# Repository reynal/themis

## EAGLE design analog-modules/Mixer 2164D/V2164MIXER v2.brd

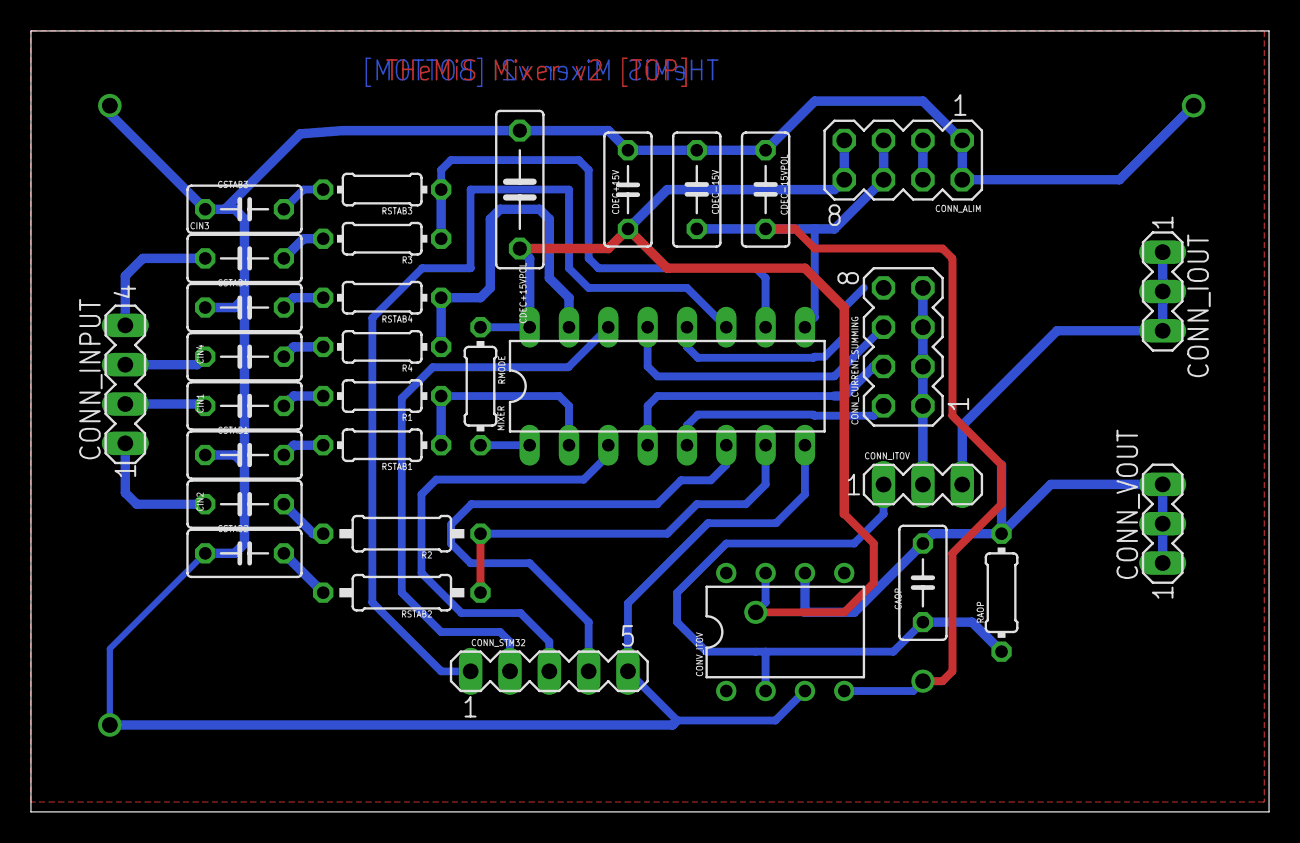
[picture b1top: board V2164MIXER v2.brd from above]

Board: 2 copper layers, 80.0 x 50.4 mm, 32 parts (0 on the bottom side), 32 nets.

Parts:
CAOP: 1p; C050-030X075
CDEC+15V: 100n; C050-030X075
CDEC+15VPOL: 100n; C075-032X103
CDEC-15V, CDEC-15VPOL: 100n; C050-030X075
CIN1, CIN2, CIN3, CIN4: 470n; C050-030X075
CONN_ALIM: MA04-2
CONN_CURRENT_SUMMING: MA04-2
CONN_INPUT: MA04-1
CONN_IOUT: MA03-1
CONN_ITOV: MA03-1
CONN_STM32: MA05-1
CONN_VOUT: MA03-1
CONV_ITOV: NE5534AN; DIL08
CSTAB1, CSTAB2, CSTAB3, CSTAB4: 560p; C050-030X075
MIXER: SSM2164_MULTI; DIL16
R1, R3, R4: 27k; 0204/7
R2: 27k; 0207/10
RAOP: 33K; 0204/7
RMODE: 8.2k; 0204/7
RSTAB1, RSTAB3, RSTAB4: 470; 0204/7
RSTAB2: 470; 0207/10

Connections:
2164_IN1: MIXER.2, R1.1, RSTAB1.1
2164_IN2: MIXER.7, R2.1, RSTAB2.1
2164_IN3: MIXER.10, R3.1, RSTAB3.1
2164_IN4: MIXER.15, R4.1, RSTAB4.1
2164_MODE: MIXER.1, RMODE.2
2164_OUT1: CONN_CURRENT_SUMMING.4, MIXER.4
2164_OUT2: CONN_CURRENT_SUMMING.2, MIXER.5
2164_OUT4: CONN_CURRENT_SUMMING.6, MIXER.13
+5V: CONN_ALIM.3, CONN_ALIM.4
+15V: CDEC+15V.2, CDEC+15VPOL.2, CONN_ALIM.7, CONN_ALIM.8, CONV_ITOV.7, MIXER.16, RMODE.1
-15V: CDEC-15V.1, CDEC-15VPOL.1, CONN_ALIM.5, CONN_ALIM.6, CONV_ITOV.4, MIXER.9
AGND: CDEC+15V.1, CDEC+15VPOL.1, CDEC-15V.2, CDEC-15VPOL.2, CONN_ALIM.1, CONN_ALIM.2, CONN_STM32.5, CONV_ITOV.3, CSTAB1.1, CSTAB2.1, CSTAB3.1, CSTAB4.1, MIXER.8
CURRENT_OUT: CONN_IOUT.1, CONN_IOUT.2, CONN_IOUT.3, CONN_ITOV.3
GAIN1: CONN_STM32.3, MIXER.3
GAIN2: CONN_STM32.4, MIXER.6
GAIN3: CONN_STM32.1, MIXER.11
GAIN4: CONN_STM32.2, MIXER.14
IN1: CIN1.1, CONN_INPUT.2
IN2: CIN2.1, CONN_INPUT.1
IN3: CIN3.1, CONN_INPUT.4
IN4: CIN4.1, CONN_INPUT.3
MIXER_OUT: CONN_CURRENT_SUMMING.1, CONN_CURRENT_SUMMING.3, CONN_CURRENT_SUMMING.5, CONN_CURRENT_SUMMING.7, CONN_ITOV.2
unnamed: CIN4.2, R4.2
unnamed: CSTAB4.2, RSTAB4.2
unnamed: CIN2.2, R2.2
unnamed: CAOP.1, CONN_ITOV.1, CONV_ITOV.2, RAOP.1
unnamed: CSTAB2.2, RSTAB2.2
unnamed: CSTAB1.2, RSTAB1.2
unnamed: CIN1.2, R1.2
unnamed: CSTAB3.2, RSTAB3.2
unnamed: CIN3.2, R3.2
VOLTAGE_OUT: CAOP.2, CONN_VOUT.1, CONN_VOUT.2, CONN_VOUT.3, CONV_ITOV.6, RAOP.2

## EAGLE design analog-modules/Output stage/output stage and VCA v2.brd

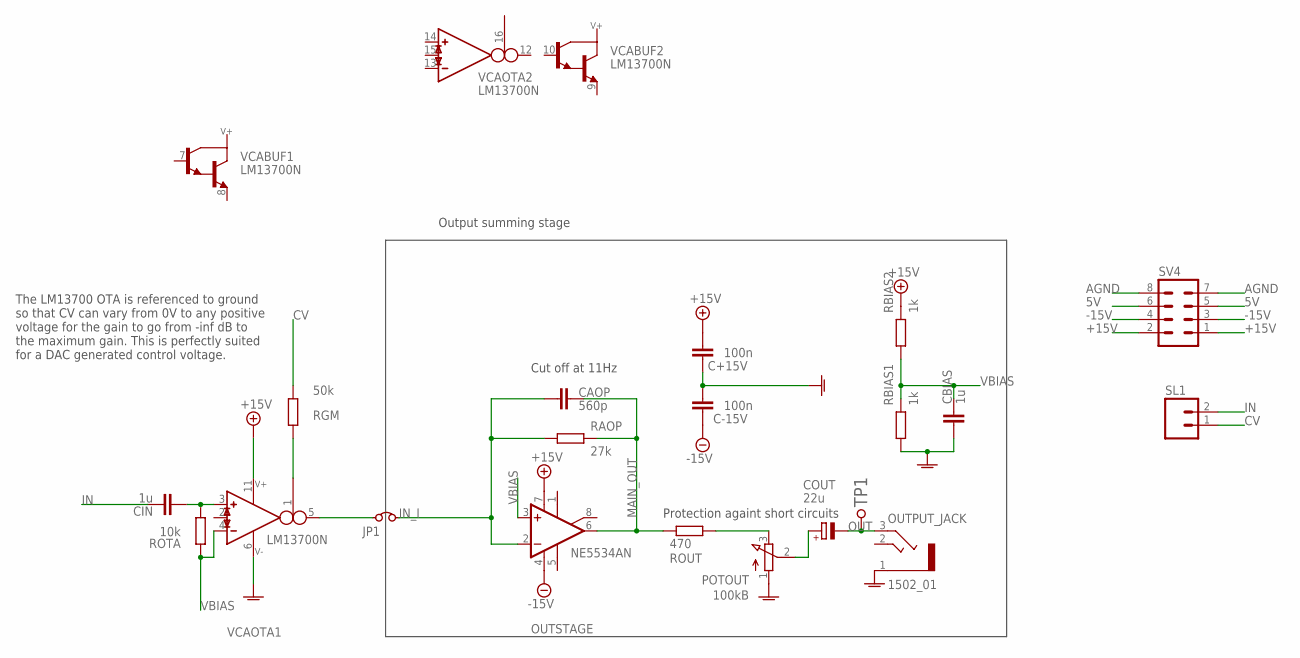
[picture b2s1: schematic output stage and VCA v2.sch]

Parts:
C+15V: 100n; C050-030X075
C-15V: 100n; C050-030X075
CAOP: 560p; C050-030X075
CBIAS: 1u; C050-030X075
CIN: 1u; C050-030X075
COUT: 22u; B45181B
JP1: JUMPER; HDR2X1
OUTPUT_JACK: 1502_01
OUTSTAGE: NE5534AN; DIL08
POTOUT: 100kB; 3RP/1610N
RAOP: 27k; 0204/7
RBIAS1, RBIAS2: 1k; 0204/7
RGM: 50k; 0204/7
ROTA: 10k; 0204/7
ROUT: 470; 0204/7
SL1: MA02; 02PA
SV4: MA04-2
TP1: TESTPOINT; TESTPOINT_63
VCA: LM13700N; DIL16

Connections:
5V: SV4.5, SV4.6
+15V: C+15V.2, OUTSTAGE.7 (V+), RBIAS2.1, SV4.1, SV4.2, VCA.11 (V+)
-15V: C-15V.1, OUTSTAGE.4 (V-), SV4.3, SV4.4
AGND: C+15V.1, C-15V.2, CBIAS.2, OUTPUT_JACK.1, POTOUT.1 (A), RBIAS1.2, SV4.7, SV4.8, VCA.6 (V-)
CV: RGM.1, SL1.1
IN: CIN.1, SL1.2
IN_I: CAOP.2, JP1.2, OUTSTAGE.2 (-IN), RAOP.2
MAIN_OUT: CAOP.1, OUTSTAGE.6 (OUT), RAOP.1, ROUT.2
unnamed: JP1.1, VCA.5 (OUT)
unnamed: RGM.2, VCA.1 (I_BIAS)
unnamed: CIN.2, ROTA.1, VCA.3 (IN_P)
unnamed: COUT.+, POTOUT.2 (S)
unnamed: POTOUT.3 (E), ROUT.1
OUT: COUT.-, OUTPUT_JACK.3 (2), TP1.P$1
VBIAS: CBIAS.1, OUTSTAGE.3 (+IN), RBIAS1.1, RBIAS2.2, ROTA.2, VCA.4 (IN_N)

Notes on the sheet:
Output summing stage
Cut off at 11Hz
Protection againt short circuits
The LM13700 OTA is referenced to ground so that CV can vary from 0V to any positive voltage for the gain to go from -inf dB to the maximum gain. This is perfectly suited for a DAC generated control voltage.

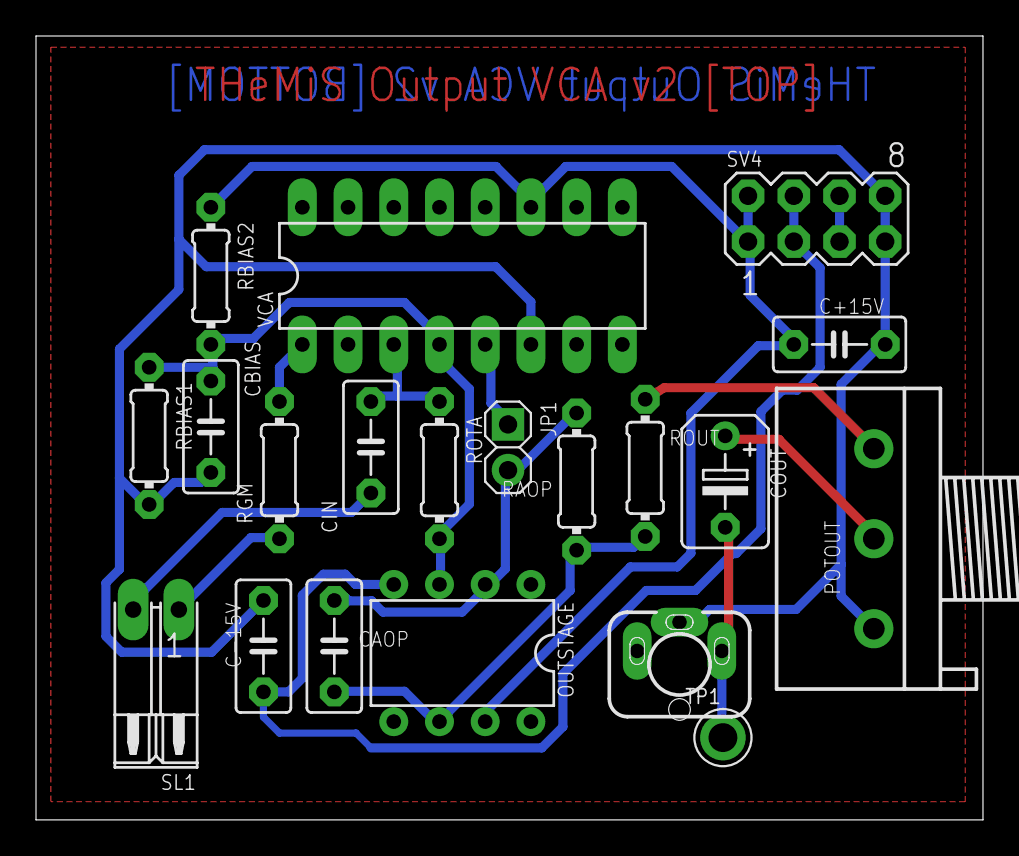
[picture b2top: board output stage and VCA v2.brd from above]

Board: 2 copper layers, 52.6 x 43.5 mm, 20 parts (0 on the bottom side), 15 nets.

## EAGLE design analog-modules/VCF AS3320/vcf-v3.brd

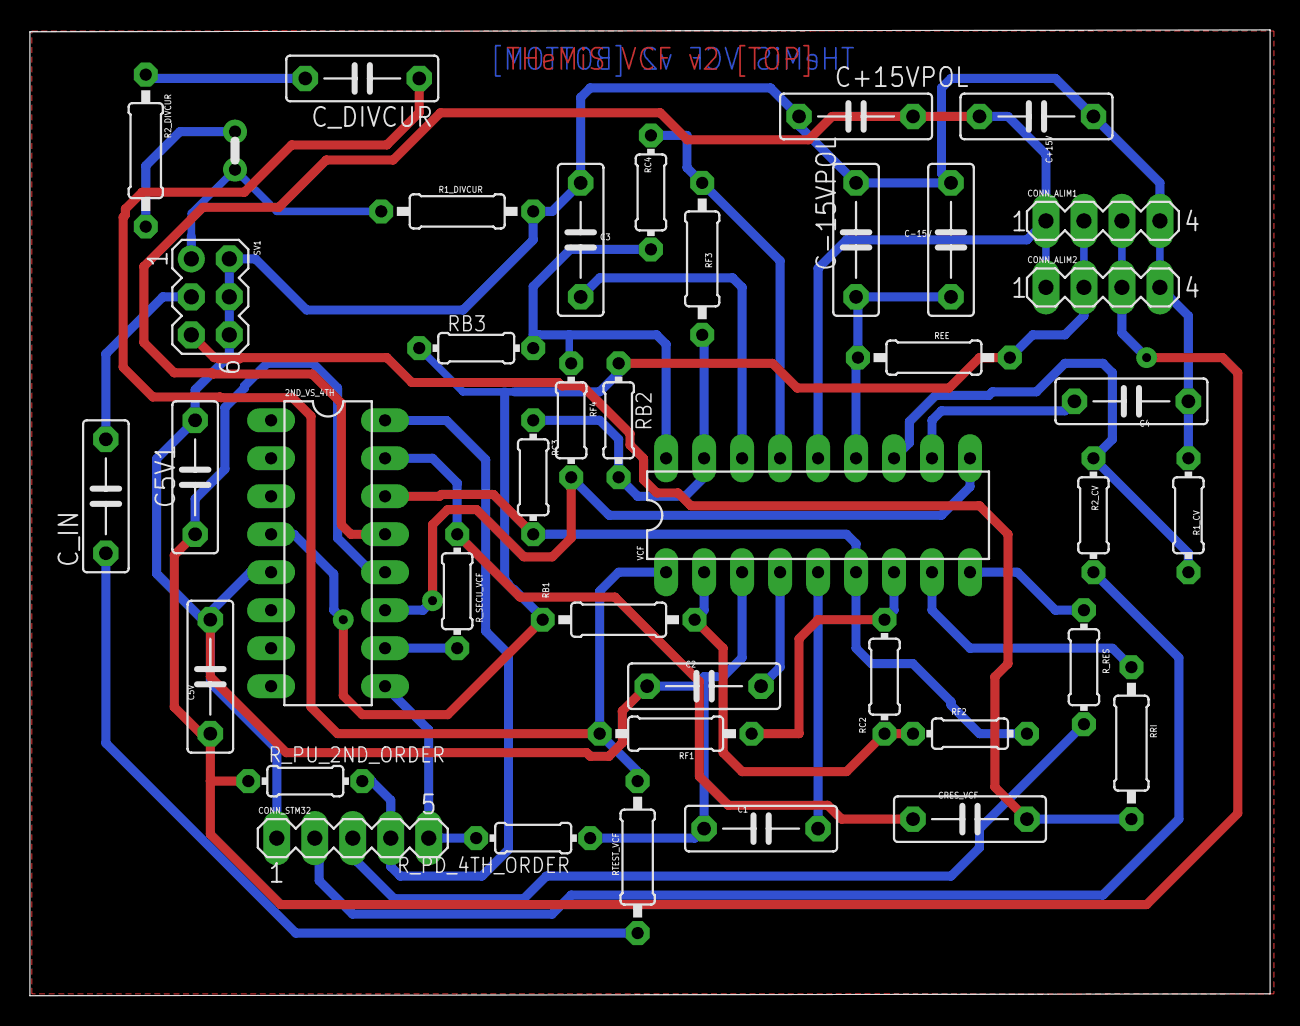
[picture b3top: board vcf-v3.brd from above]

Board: 2 copper layers, 82.9 x 64.6 mm, 41 parts (0 on the bottom side), 32 nets.

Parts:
2ND_VS_4TH: ADG411N; DIL16
C1, C2, C3, C4: 300p; C075-032X103
C5V, C5V1: 100n; C075-032X103
C+15V: 100n; C075-032X103
C+15VPOL: 1u; C075-032X103
C-15V: 100n; C075-032X103
C-15VPOL: 1u; C075-032X103
CONN_ALIM1, CONN_ALIM2: MA04-1
CONN_STM32: MA05-1
CRES_VCF: 1u; C075-032X103
C_DIVCUR: 1u; C075-032X103
C_IN: 470n; C075-032X103
JP_MIXER_OUT: JUMPER_WIRE; JUMPER
R1_CV: 10k; 0204/7
R1_DIVCUR, R2_DIVCUR: 470; 0207/10
R2_CV: 100k; 0204/7
RB1: 220k; 0207/10
RB2, RB3: 220k; 0204/7
RC2, RC3, RC4: 91k; 0204/7
REE: 1.5k; 0207/10
RF1, RF3: 100k; 0207/10
RF2, RF4: 100k; 0204/7
RRI: 51k; 0207/10
RTEST_VCF: 91k; 0207/10
R_PD_4TH_ORDER: 100k; 0204/7
R_PU_2ND_ORDER: 100k; 0204/7
R_RES: 100k; 0204/7
R_SECU_VCF: 1k; 0204/7
SV1: MA03-2
VCF: AS3320; DIL18

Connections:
5V: 2ND_VS_4TH.12, C5V.1, C5V1.1, CONN_ALIM1.3, CONN_ALIM2.3, R_PU_2ND_ORDER.1
+15V: 2ND_VS_4TH.13, C+15V.2, C+15VPOL.2, CONN_ALIM1.1, CONN_ALIM2.1, VCF.14
-15V: 2ND_VS_4TH.4, CONN_ALIM1.2, CONN_ALIM2.2, RB1.1, RB2.1, RB3.1, REE.1
AGND: 2ND_VS_4TH.5, C1.1, C2.1, C3.1, C4.1, C5V.2, C5V1.2, C+15V.1, C+15VPOL.1, C-15V.2, C-15VPOL.2, CONN_ALIM1.4, CONN_ALIM2.4, CONN_STM32.1, R1_CV.2, R1_DIVCUR.2, R_PD_4TH_ORDER.1, SV1.2, SV1.4, SV1.6, VCF.3
CV_CUTOFF: CONN_STM32.2, R2_CV.2
CV_RES: CONN_STM32.3, R_RES.2
IN2: RB1.2, RC2.1, RF2.1, VCF.2
IN3: RB2.2, RC3.1, RF3.1, VCF.17
IN4: RB3.2, RC4.1, RF4.1, VCF.18
IN_2NDORDER: 2ND_VS_4TH.16, CONN_STM32.4, R_PU_2ND_ORDER.2
IN_4THORDER: 2ND_VS_4TH.9, CONN_STM32.5, R_PD_4TH_ORDER.2
I_IN: JP_MIXER_OUT.1, R1_DIVCUR.1, SV1.1
unnamed: C_IN.1, RTEST_VCF.1
unnamed: 2ND_VS_4TH.15, CRES_VCF.1, R_SECU_VCF.1
unnamed: 2ND_VS_4TH.10, R_SECU_VCF.2
unnamed: C_DIVCUR.2, R2_DIVCUR.1
unnamed: JP_MIXER_OUT.2, R2_DIVCUR.2
OUT: CRES_VCF.2, RRI.2, SV1.5
OUT1: RC2.2, RF1.1, VCF.7
OUT2: 2ND_VS_4TH.14, RC3.2, RF2.2, VCF.6
OUT3: RC4.2, RF3.2, VCF.15
OUT4: 2ND_VS_4TH.11, RF4.2, VCF.10
VCAP1: C1.2, VCF.5
VCAP2: C2.2, VCF.4
VCAP3: C3.2, VCF.16
VCAP4: C4.2, VCF.11
VCF_FREQ_CV: R1_CV.1, R2_CV.1, VCF.12
VCF_IN: C_DIVCUR.1, RF1.2, RTEST_VCF.2, VCF.1
VCF_RES_CUR: R_RES.1, VCF.9
VEE: C-15V.1, C-15VPOL.1, REE.2, VCF.13
VIN_RES: RRI.1, VCF.8
V_IN: C_IN.2, SV1.3

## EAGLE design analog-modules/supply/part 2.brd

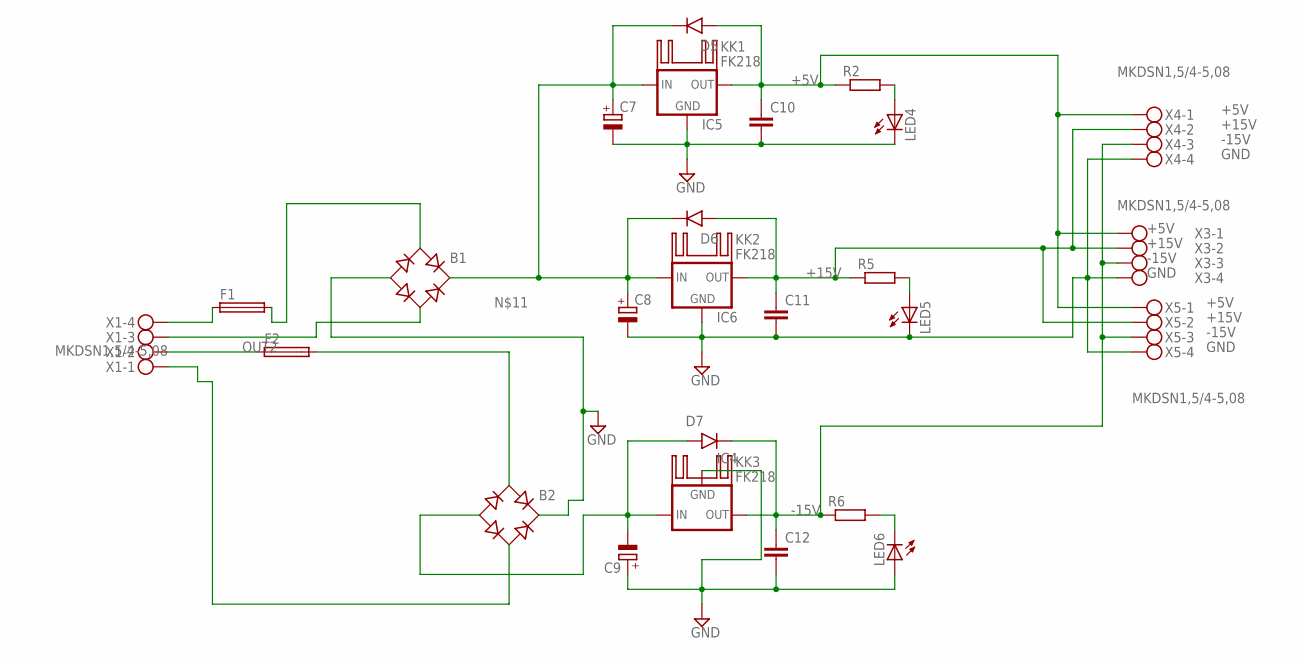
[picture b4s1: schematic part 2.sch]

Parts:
B1, B2: RB1A
C7, C8, C9: CPOL-EUE7.5-18; E7,5-18
C10, C11, C12: C-EU050-025X075; C050-025X075
D5, D6, D7: 1N4001; DO41-10
F1, F2: SH22,5A
IC4: 79XXS
IC5, IC6: 78XXS
KK1, KK2, KK3: FK218
LED4, LED5, LED6: LED5MM
R2, R5, R6: R-EU_0207/15; 0207/15
X1, X3, X4, X5: MKDSN1,5/4-5,08

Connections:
+5V: C10.1, D5.A (ANODE), IC5.OUT, R2.1, X3.1, X4.1, X5.1
+15V: C11.1, D6.A (ANODE), IC6.OUT, R5.1, X3.2, X4.2, X5.2
-15V: C12.1, D7.C (CATHODE), IC4.OUT, R6.1, X3.3, X4.3, X5.3
GND: B1.-, B2.+, C7.-, C8.-, C9.+, C10.2, C11.2, C12.2, IC4.GND, IC5.GND, IC6.GND, LED4.K (C), LED5.K (C), LED6.A, X3.4, X4.4, X5.4
unnamed: B1.AC1, F1.2
unnamed: F1.1, X1.4
unnamed: F2.1, X1.2
unnamed: B2.AC2, X1.1
unnamed: LED5.A, R5.2
unnamed: B2.-, C9.-, D7.A (ANODE), IC4.IN
unnamed: B1.+, C7.+, C8.+, D5.C (CATHODE), D6.C (CATHODE), IC5.IN, IC6.IN
unnamed: B2.AC1, F2.2
unnamed: LED4.A, R2.2
unnamed: LED6.K (C), R6.2
OUT2: B1.AC2, X1.3

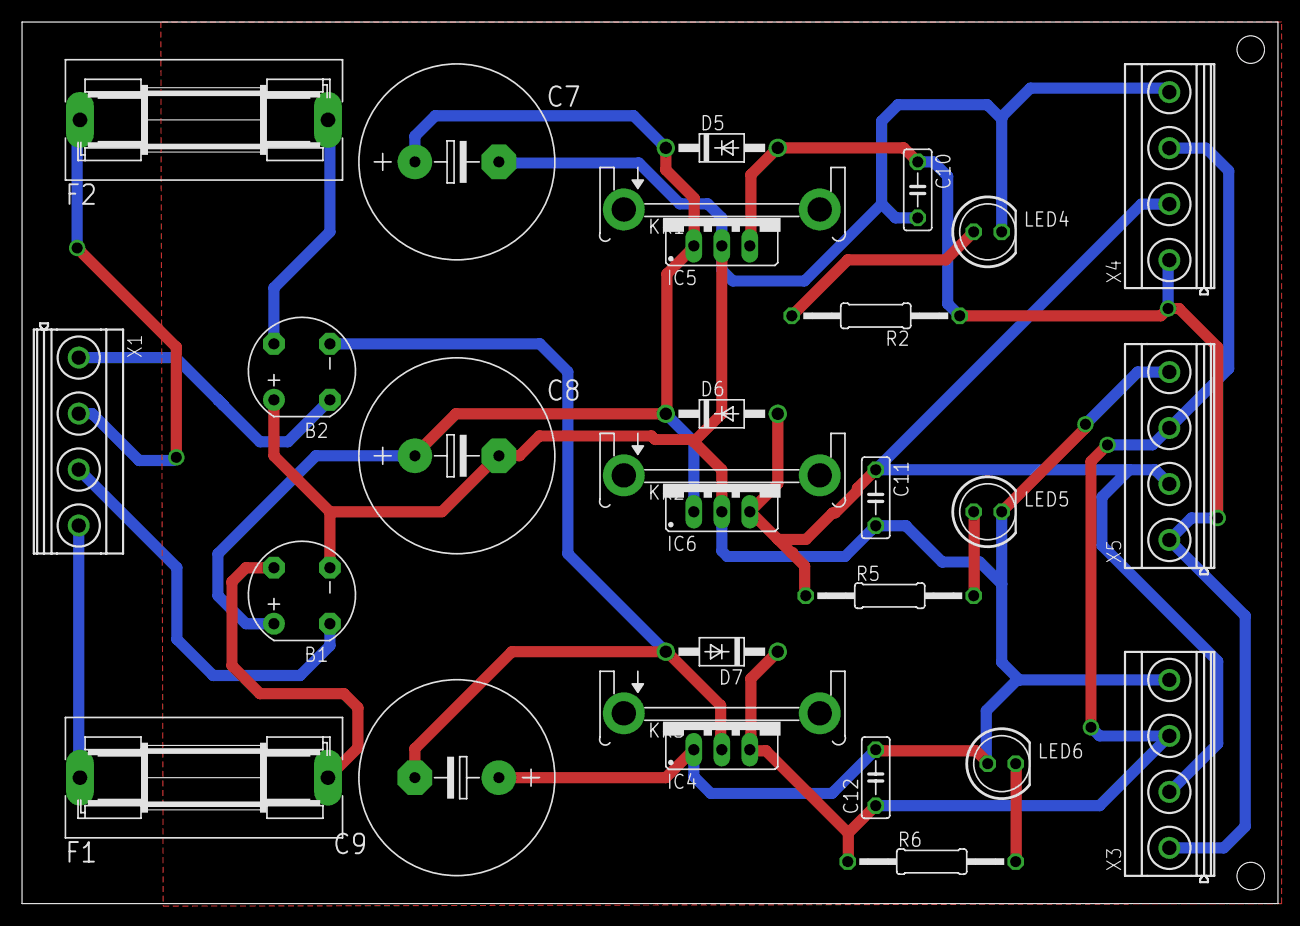
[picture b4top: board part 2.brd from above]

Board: 2 copper layers, 114.0 x 80.0 mm, 29 parts (0 on the bottom side), 15 nets.

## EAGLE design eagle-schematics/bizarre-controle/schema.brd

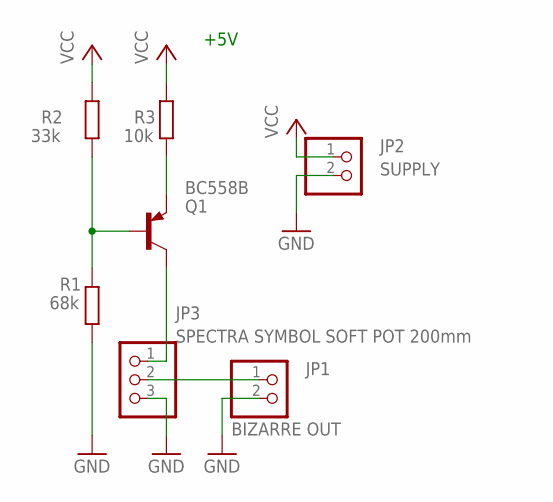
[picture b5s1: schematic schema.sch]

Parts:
JP1: BIZARRE OUT; 1X02
JP2: SUPPLY; 1X02
JP3: SPECTRA SYMBOL SOFT POT 200mm; 1X03
Q1: BC558B; TO92-EBC
R1: 68k; 0309/10
R2: 33k; 0309/10
R3: 10k; 0309/10

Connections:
GND: JP1.2, JP2.2, JP3.3, R1.1
unnamed: Q1.B, R1.2, R2.1
unnamed: Q1.E, R3.1
unnamed: JP3.1, Q1.C
unnamed: JP1.1, JP3.2
VCC: JP2.1, R2.2, R3.2

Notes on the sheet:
+5V

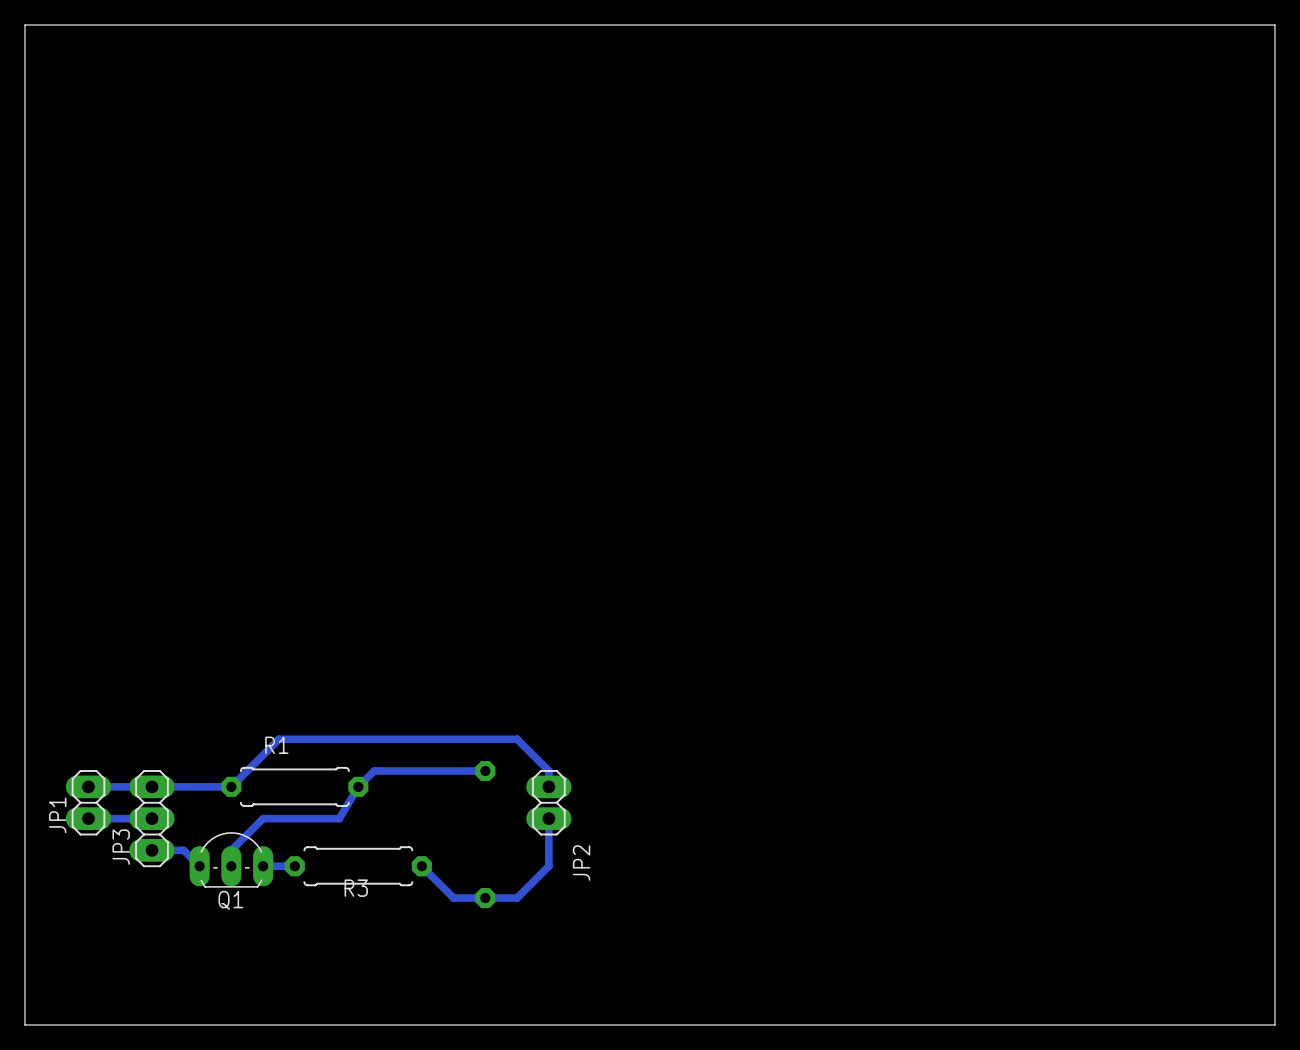
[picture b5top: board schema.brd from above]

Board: 2 copper layers, 100.0 x 80.0 mm, 7 parts (1 on the bottom side), 6 nets.

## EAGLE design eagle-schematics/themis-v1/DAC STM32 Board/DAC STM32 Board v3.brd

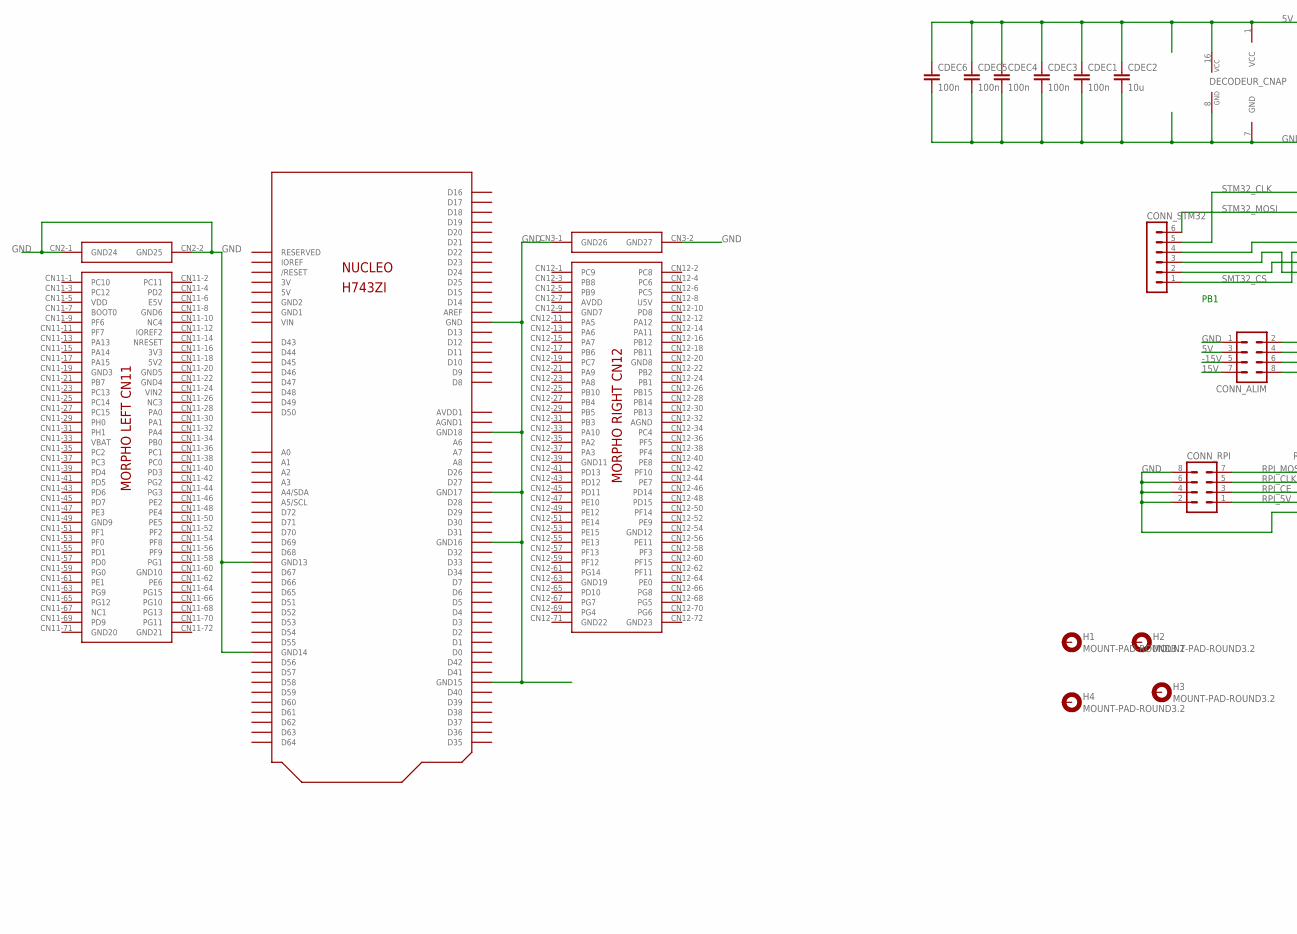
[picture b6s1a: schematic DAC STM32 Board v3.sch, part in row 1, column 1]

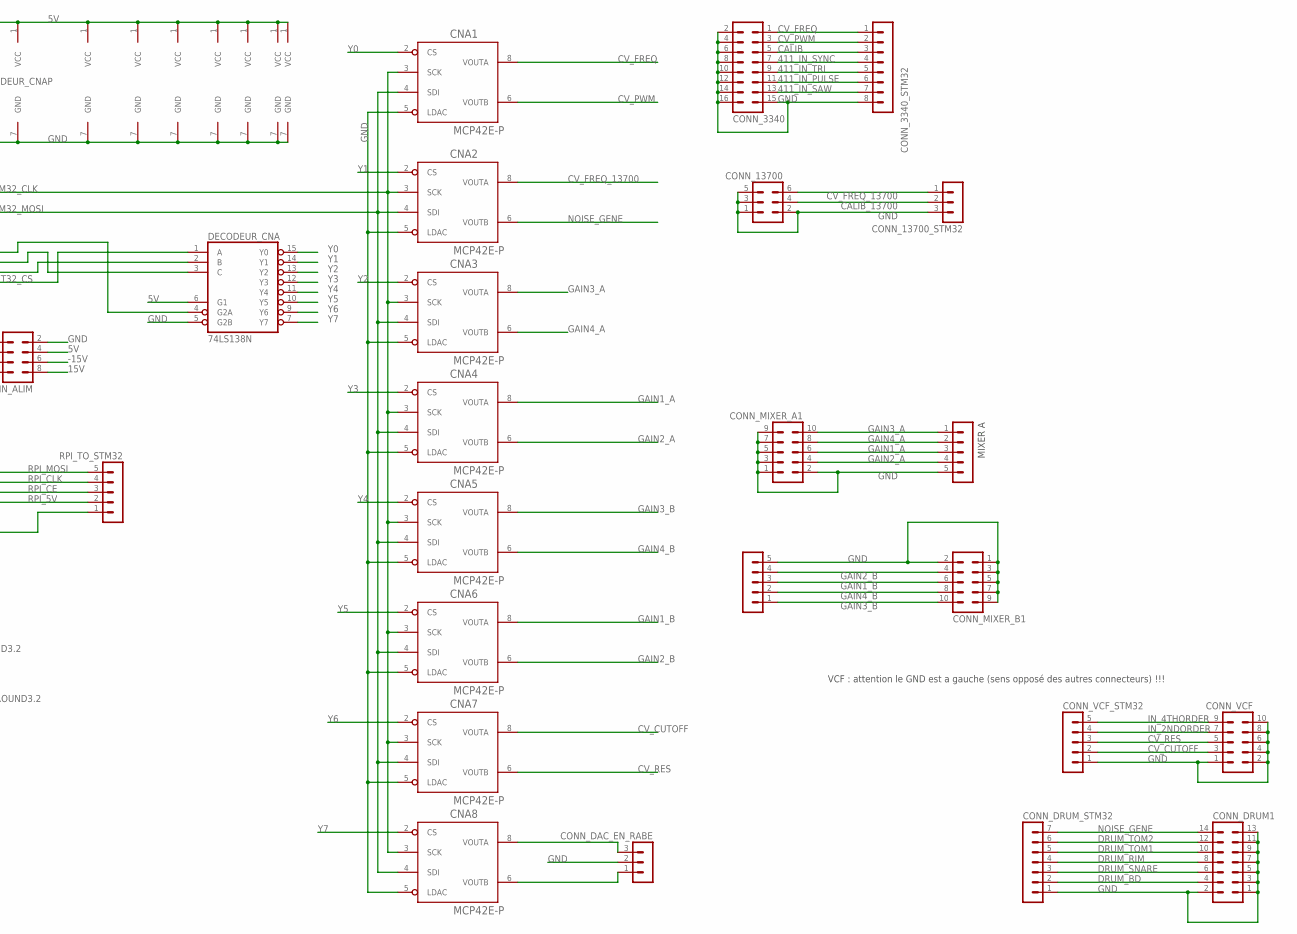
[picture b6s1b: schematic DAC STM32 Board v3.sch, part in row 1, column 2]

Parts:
CDEC1: 100n; C050-025X075
CDEC2: 10u; C050-025X075
CDEC3, CDEC4, CDEC5, CDEC6: 100n; C075-032X103
CNA1, CNA2, CNA3, CNA4, CNA5, CNA6, CNA7, CNA8: MCP42E-P; DIL08
CONN_3340: MA08-2
CONN_3340_STM32: MA08-1
CONN_13700: MA03-2
CONN_13700_STM32: MA03-1
CONN_ALIM: MA04-2
CONN_DAC_EN_RABE: MA03-1
CONN_DRUM1: MA07-2
CONN_DRUM_STM32: MA07-1
CONN_MIXER_A1: MA05-2
CONN_MIXER_A_STM32: MA05-1
CONN_MIXER_B1: MA05-2
CONN_MIXER_B_STM32: MA05-1
CONN_RPI: MA04-2
CONN_STM32: MA06-1
CONN_VCF: MA05-2
CONN_VCF_STM32: MA05-1
DECODEUR_CNA: 74LS138N; DIL16
H1, H2, H3, H4: MOUNT-PAD-ROUND3.2; 3,2-PAD
RPI_TO_STM32: MA05-1
U$1: NUCLEO_H743ZI; NUCLEO_BRD144

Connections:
3V: U$1.CN8-7 (3V)
3V3: U$1.CN11-16 (3V3)
5V: CDEC1.1, CDEC2.1, CDEC3.1, CDEC4.1, CDEC5.1, CDEC6.1, CNA1.1 (VCC), CNA2.1 (VCC), CNA3.1 (VCC), CNA4.1 (VCC), CNA5.1 (VCC), CNA6.1 (VCC), CNA7.1 (VCC), CNA8.1 (VCC), CONN_ALIM.3, CONN_ALIM.4, DECODEUR_CNA.6 (G1), DECODEUR_CNA.16 (VCC), U$1.CN8-9 (5V)
5V2: U$1.CN11-18 (5V2)
15V: CONN_ALIM.7, CONN_ALIM.8
411_IN_PULSE: CONN_3340.11, CONN_3340_STM32.6
411_IN_SAW: CONN_3340.13, CONN_3340_STM32.7
411_IN_SYNC: CONN_3340.7, CONN_3340_STM32.4
411_IN_TRI: CONN_3340.9, CONN_3340_STM32.5
-15V: CONN_ALIM.5, CONN_ALIM.6
AGND: U$1.CN12-32 (AGND)
AVDD: U$1.CN12-7 (AVDD)
CALIB: CONN_3340.5, CONN_3340_STM32.3
CALIB_13700: CONN_13700.4, CONN_13700_STM32.2
CV_CUTOFF: CNA7.8 (VOUTA), CONN_VCF.3, CONN_VCF_STM32.2
CV_FREQ: CNA1.8 (VOUTA), CONN_3340.1, CONN_3340_STM32.1
CV_FREQ_13700: CNA2.8 (VOUTA), CONN_13700.6, CONN_13700_STM32.1
CV_PWM: CNA1.6 (VOUTB), CONN_3340.3, CONN_3340_STM32.2
CV_RES: CNA7.6 (VOUTB), CONN_VCF.5, CONN_VCF_STM32.3
D21: U$1.CN7-11 (D21)
DRUM_BD: CONN_DRUM1.4, CONN_DRUM_STM32.2
DRUM_RIM: CONN_DRUM1.8, CONN_DRUM_STM32.4
DRUM_SNARE: CONN_DRUM1.6, CONN_DRUM_STM32.3
DRUM_TOM1: CONN_DRUM1.10, CONN_DRUM_STM32.5
DRUM_TOM2: CONN_DRUM1.12, CONN_DRUM_STM32.6
E5V: U$1.CN11-6 (E5V)
GAIN1_A: CNA4.8 (VOUTA), CONN_MIXER_A1.6, CONN_MIXER_A_STM32.3
GAIN1_B: CNA6.8 (VOUTA), CONN_MIXER_B1.6, CONN_MIXER_B_STM32.3
GAIN2_A: CNA4.6 (VOUTB), CONN_MIXER_A1.4, CONN_MIXER_A_STM32.4
GAIN2_B: CNA6.6 (VOUTB), CONN_MIXER_B1.4, CONN_MIXER_B_STM32.4
GAIN3_A: CNA3.8 (VOUTA), CONN_MIXER_A1.10, CONN_MIXER_A_STM32.1
GAIN3_B: CNA5.8 (VOUTA), CONN_MIXER_B1.10, CONN_MIXER_B_STM32.1
GAIN4_A: CNA3.6 (VOUTB), CONN_MIXER_A1.8, CONN_MIXER_A_STM32.2
GAIN4_B: CNA5.6 (VOUTB), CONN_MIXER_B1.8, CONN_MIXER_B_STM32.2
GND: CDEC1.2, CDEC2.2, CDEC3.2, CDEC4.2, CDEC5.2, CDEC6.2, CNA1.5 (LDAC), CNA1.7 (GND), CNA2.5 (LDAC), CNA2.7 (GND), CNA3.5 (LDAC), CNA3.7 (GND), CNA4.5 (LDAC), CNA4.7 (GND), CNA5.5 (LDAC), CNA5.7 (GND), CNA6.5 (LDAC), CNA6.7 (GND), CNA7.5 (LDAC), CNA7.7 (GND), CNA8.5 (LDAC), CNA8.7 (GND), CONN_3340.2, CONN_3340.4, CONN_3340.6, CONN_3340.8, CONN_3340.10, CONN_3340.12, CONN_3340.14, CONN_3340.15, CONN_3340.16, CONN_3340_STM32.8, CONN_13700.1, CONN_13700.2, CONN_13700.3, CONN_13700.5, CONN_13700_STM32.3, CONN_ALIM.1, CONN_ALIM.2, CONN_DAC_EN_RABE.2, CONN_DRUM1.1, CONN_DRUM1.2, CONN_DRUM1.3, CONN_DRUM1.5, CONN_DRUM1.7, CONN_DRUM1.9, CONN_DRUM1.11, CONN_DRUM1.13, CONN_DRUM_STM32.1, CONN_MIXER_A1.1, CONN_MIXER_A1.2, CONN_MIXER_A1.3, CONN_MIXER_A1.5, CONN_MIXER_A1.7, CONN_MIXER_A1.9, CONN_MIXER_A_STM32.5, CONN_MIXER_B1.1, CONN_MIXER_B1.2, CONN_MIXER_B1.3, CONN_MIXER_B1.5, CONN_MIXER_B1.7, CONN_MIXER_B1.9, CONN_MIXER_B_STM32.5, CONN_RPI.2, CONN_RPI.4, CONN_RPI.6, CONN_RPI.8, CONN_VCF.1, CONN_VCF.2, CONN_VCF.4, CONN_VCF.6, CONN_VCF.8, CONN_VCF.10, CONN_VCF_STM32.1, DECODEUR_CNA.5 (G2B), DECODEUR_CNA.8 (GND), RPI_TO_STM32.1, U$1.CN2-1 (GND24), U$1.CN2-2 (GND25), U$1.CN3-1 (GND26), U$1.CN3-2 (GND27), U$1.CN7-8 (GND), U$1.CN9-12 (GND14), U$1.CN9-23 (GND13), U$1.CN10-5 (GND18), U$1.CN10-17 (GND17), U$1.CN10-22 (GND15), U$1.CN10-27 (GND16)
GND1: U$1.CN8-13 (GND1)
GND2: U$1.CN8-11 (GND2)
GND3: U$1.CN11-19 (GND3)
GND4: U$1.CN11-22 (GND4)
GND5: U$1.CN11-20 (GND5)
GND6: U$1.CN11-8 (GND6)
GND7: U$1.CN12-9 (GND7)
GND8: U$1.CN12-20 (GND8)
IN_2NDORDER: CONN_VCF.7, CONN_VCF_STM32.4
IN_4THORDER: CONN_VCF.9, CONN_VCF_STM32.5
unnamed: CONN_STM32.1, DECODEUR_CNA.1 (A)
unnamed: CONN_STM32.2, DECODEUR_CNA.2 (B)
unnamed: CONN_STM32.3, DECODEUR_CNA.3 (C)
unnamed: CNA8.8 (VOUTA), CONN_DAC_EN_RABE.3
unnamed: CNA8.6 (VOUTB), CONN_DAC_EN_RABE.1
NOISE_GENE: CNA2.6 (VOUTB), CONN_DRUM1.14, CONN_DRUM_STM32.7
RPI_5V: CONN_RPI.1, RPI_TO_STM32.2
RPI_CE: CONN_RPI.3, RPI_TO_STM32.3
RPI_CLK: CONN_RPI.5, RPI_TO_STM32.4
RPI_MOSI: CONN_RPI.7, RPI_TO_STM32.5
SMT32_CS: CONN_STM32.4, DECODEUR_CNA.4 (G2A)
STM32_CLK: CNA1.3 (SCK), CNA2.3 (SCK), CNA3.3 (SCK), CNA4.3 (SCK), CNA5.3 (SCK), CNA6.3 (SCK), CNA7.3 (SCK), CNA8.3 (SCK), CONN_STM32.5
STM32_MOSI: CNA1.4 (SDI), CNA2.4 (SDI), CNA3.4 (SDI), CNA4.4 (SDI), CNA5.4 (SDI), CNA6.4 (SDI), CNA7.4 (SDI), CNA8.4 (SDI), CONN_STM32.6
U5V: U$1.CN12-8 (U5V)
VBAT: U$1.CN11-33 (VBAT)
VDD: U$1.CN11-5 (VDD)
VIN: U$1.CN8-15 (VIN)
VIN2: U$1.CN11-24 (VIN2)
Y0: CNA1.2 (CS), DECODEUR_CNA.15 (Y0)
Y1: CNA2.2 (CS), DECODEUR_CNA.14 (Y1)
Y2: CNA3.2 (CS), DECODEUR_CNA.13 (Y2)
Y3: CNA4.2 (CS), DECODEUR_CNA.12 (Y3)
Y4: CNA5.2 (CS), DECODEUR_CNA.11 (Y4)
Y5: CNA6.2 (CS), DECODEUR_CNA.10 (Y5)
Y6: CNA7.2 (CS), DECODEUR_CNA.9 (Y6)
Y7: CNA8.2 (CS), DECODEUR_CNA.7 (Y7)

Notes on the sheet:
MIXER A
PB1
VCF : attention le GND est a gauche (sens opposé des autres connecteurs) !!!

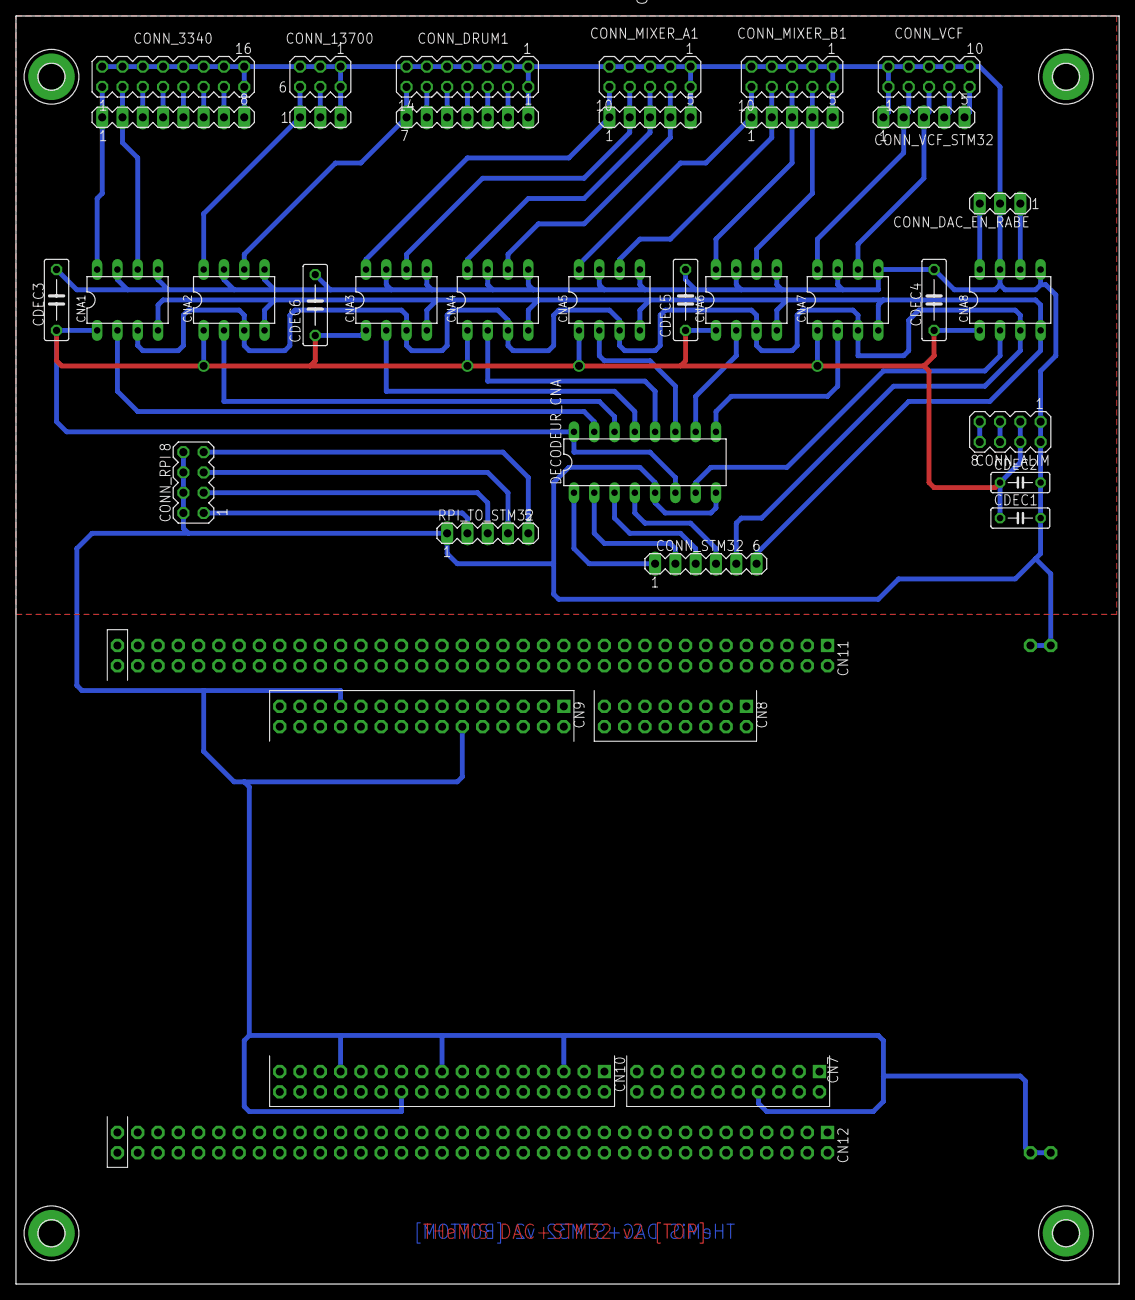
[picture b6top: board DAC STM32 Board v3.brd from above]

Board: 2 copper layers, 138.1 x 158.7 mm, 37 parts (0 on the bottom side), 51 nets.
